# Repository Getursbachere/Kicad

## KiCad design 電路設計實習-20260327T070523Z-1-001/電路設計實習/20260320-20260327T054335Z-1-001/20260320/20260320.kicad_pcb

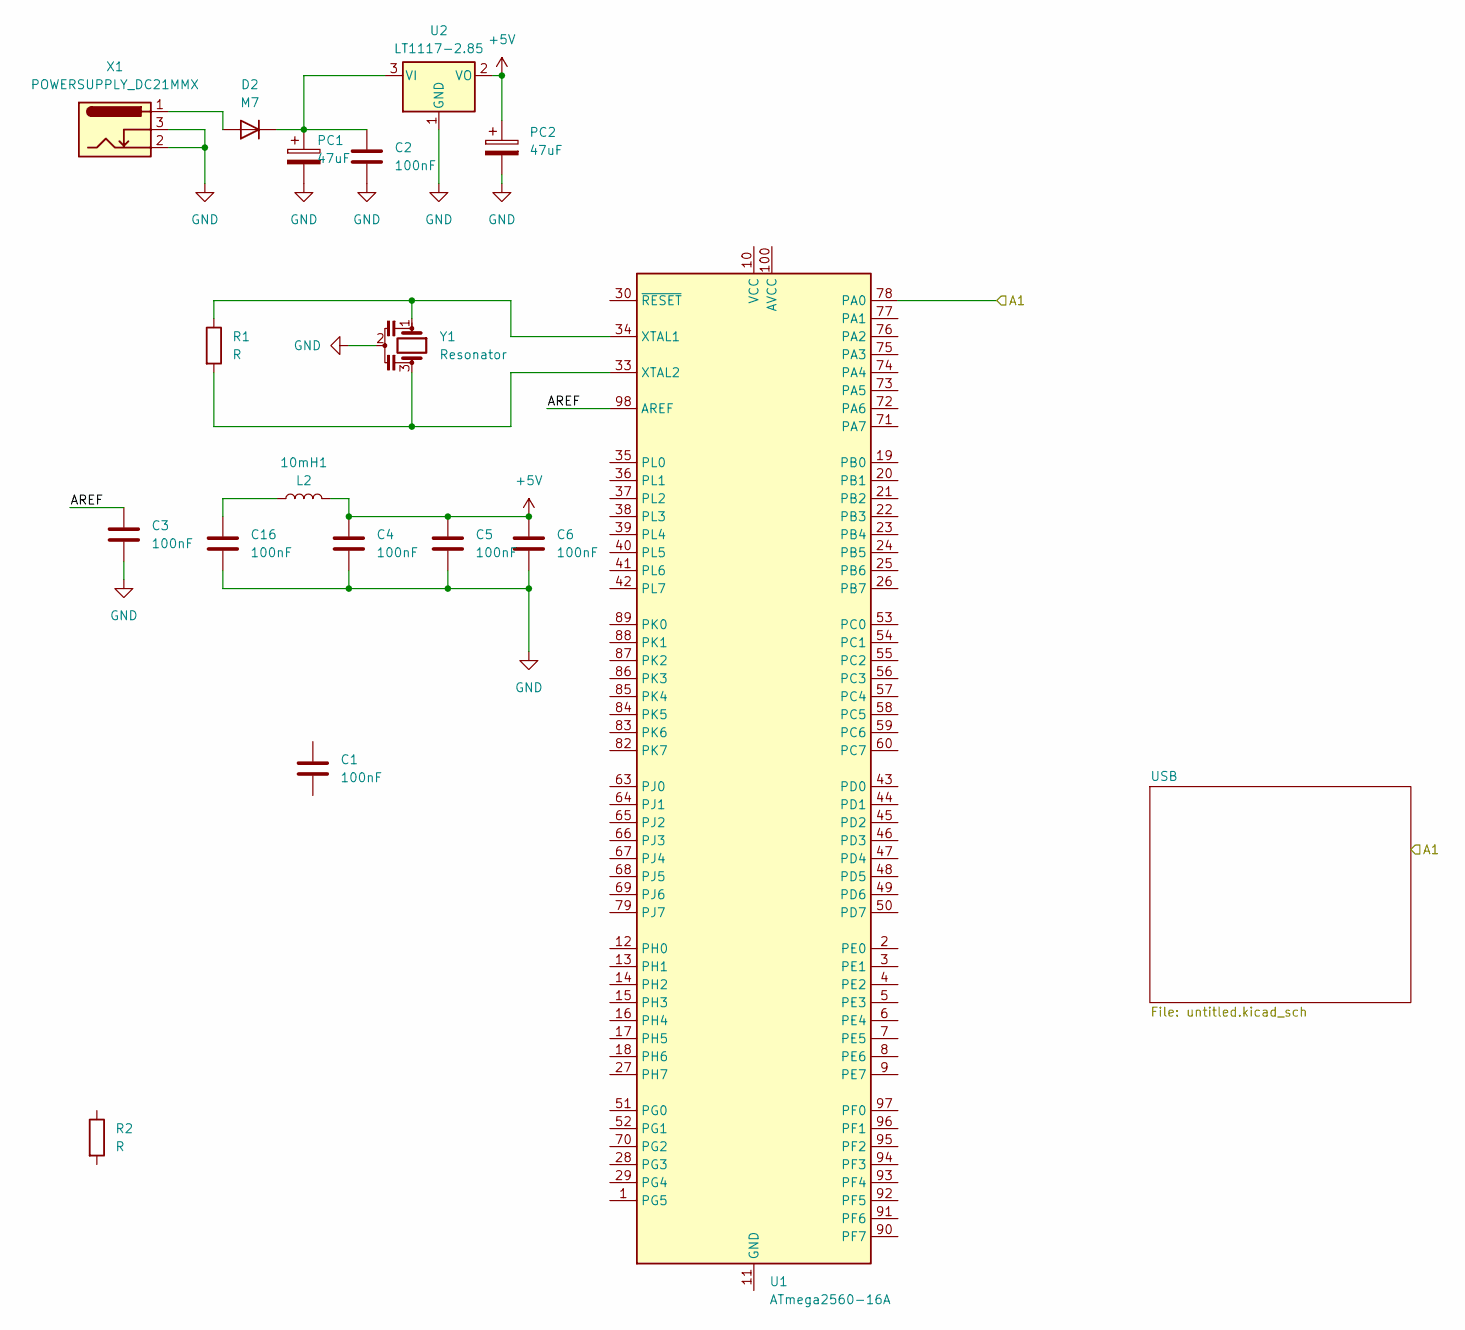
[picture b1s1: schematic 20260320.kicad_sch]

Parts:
10mH1: L2; L_0805_2012Metric
C1, C2, C3, C4, C5, C6, C16: 100nF; C_0603_1608Metric
D2: M7; D_SMB
PC1, PC2: 47uF; CP_Radial_D6.3mm_P2.50mm
R1, R2: R; R_0603_1608Metric
U1: ATmega2560-16A; TQFP-100_14x14mm_P0.5mm
U2: LT1117-2.85; SOT-223-3_TabPin2
X1: POWERSUPPLY_DC21MMX; BarrelJack_CUI_PJ-102AH_Horizontal
Y1: Resonator; Resonator_SMD_Murata_CSTxExxV-3Pin_3.0x1.1mm

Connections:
+5V: 10mH1.2, C4.1, C5.1, C6.1, PC2.1, U2.2 (VO); also elsewhere on the board
/A1: U1.78 (PA0)
/AREF: C3.1, U1.98 (AREF)
GND: C2.2, C3.2, C4.2, C5.2, C6.2, C16.2, PC1.2, PC2.2, U2.1 (GND), X1.2, X1.3, Y1.2; also elsewhere on the board
unnamed: 10mH1.1, C16.1
unnamed: D2.2 (A), X1.1
unnamed: C2.1, D2.1 (K), PC1.1, U2.3 (VI)
unnamed: U1.11 (GND), U1.32 (GND), U1.62 (GND), U1.81 (GND), U1.99 (GND)
unnamed: U1.10 (VCC), U1.31 (VCC), U1.61 (VCC), U1.80 (VCC)
unnamed: R1.1, U1.34 (XTAL1), Y1.1
unnamed: R1.2, U1.33 (XTAL2), Y1.3

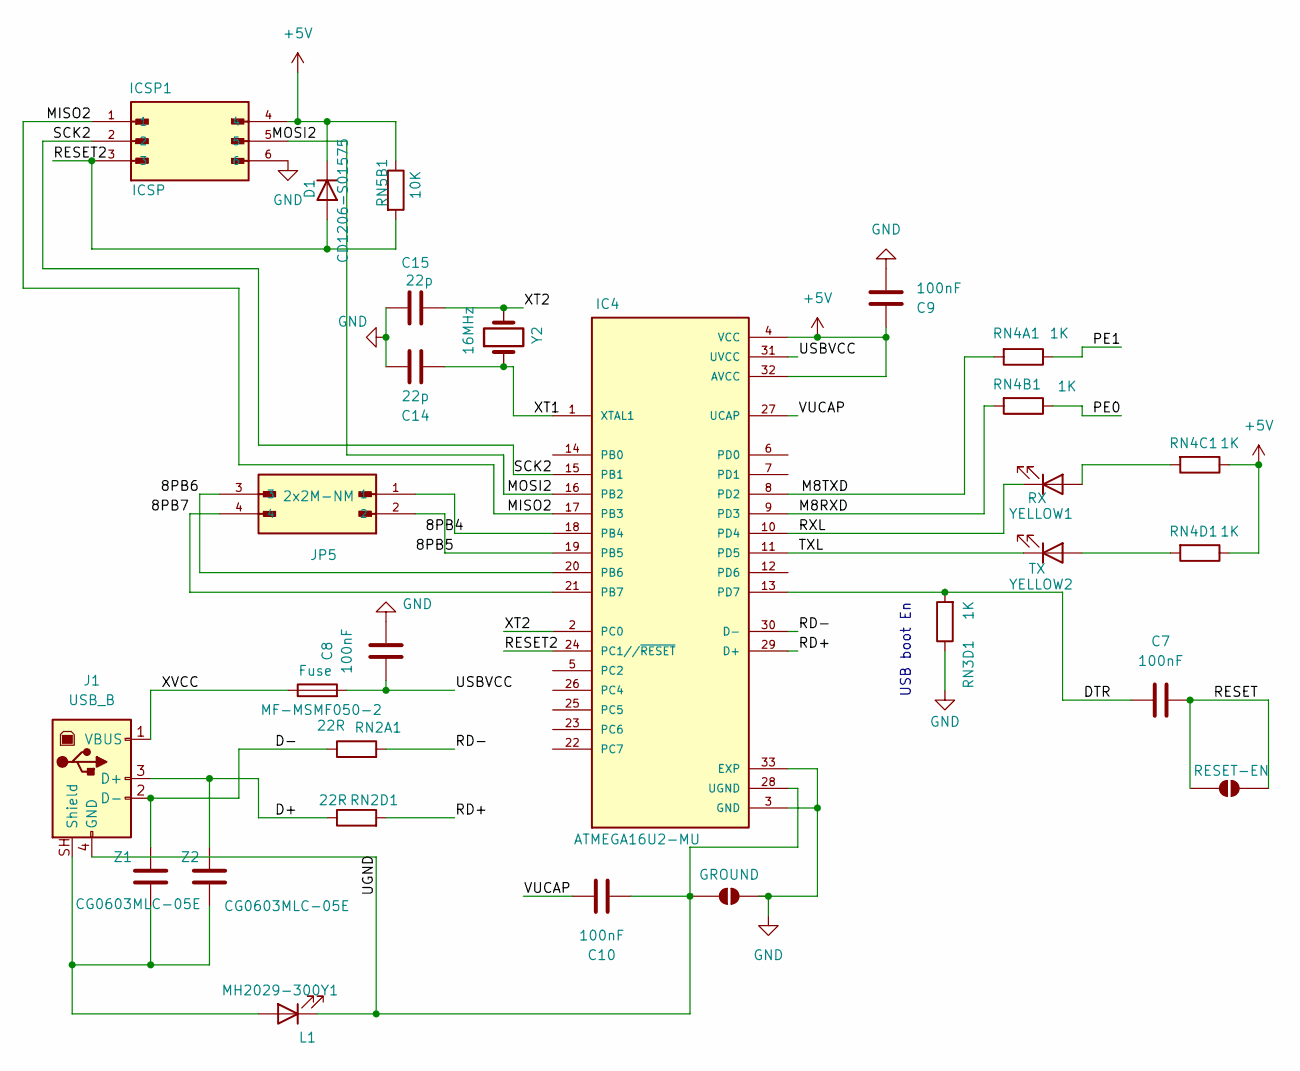
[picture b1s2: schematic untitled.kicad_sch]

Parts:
C7, C8, C9, C10: 100nF; C_0603_1608Metric
C14, C15: 22p; C_0603_1608Metric
D1: CD1206-S01575; D_MicroMELF
IC4: ATMEGA16U2-MU; QFN-32-1EP_5x5mm_P0.5mm_EP3.45x3.45mm
ICSP1: ICSP; MOLEX_2068320602; PARTREV A3
J1: USB_B; USB_B_Lumberg_2411_02_Horizontal
JP1: RESET-EN; SolderJumper-2_P1.3mm_Open_RoundedPad1.0x1.5mm
JP5: 2x2M-NM; PinHeader_2x02_P2.54mm_Vertical; PARTREV A3
MF-MSMF050-2: Fuse; Fuse_1812_4532Metric
MH2029-300Y1: L1; LED_0805_2012Metric
RN2A1, RN2D1: 22R; R_Array_SIP8
RN3D1, RN4A1, RN4B1, RN4C1, RN4D1: 1K; R_Array_SIP8
RN5B1: 10K; R_Array_SIP8
Y2: 16MHz; Crystal_SMD_0603-2Pin_6.0x3.5mm
YELLOW1: RX; LED_0805_2012Metric
YELLOW2: TX; LED_0805_2012Metric
Z1, Z2: CG0603MLC-05E; C_0603_1608Metric
a1: GROUND

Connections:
+5V: C9.1, D1.1 (K), IC4.4 (VCC), IC4.32 (AVCC), ICSP1.4, RN4C1.1, RN4D1.1, RN5B1.1; also elsewhere on the board
/USB/8PB4: IC4.18 (PB4), JP5.1
/USB/8PB5: IC4.19 (PB5), JP5.2
/USB/8PB6: IC4.20 (PB6), JP5.3
/USB/8PB7: IC4.21 (PB7), JP5.4
/USB/D+: J1.3 (D+), RN2D1.1, Z2.1
/USB/D-: J1.2 (D-), RN2A1.1, Z1.2
/USB/DTR: C7.1, IC4.13 (PD7), RN3D1.2
/USB/M8RXD: IC4.9 (PD3), RN4B1.2
/USB/M8TXD: IC4.8 (PD2), RN4A1.2
/USB/MISO2: IC4.17 (PB3), ICSP1.1
/USB/MOSI2: IC4.16 (PB2), ICSP1.5
/USB/PE0: RN4B1.1
/USB/PE1: RN4A1.1
/USB/RD+: IC4.29 (D+), RN2D1.2
/USB/RD-: IC4.30 (D-), RN2A1.2
/USB/RESET: C7.2, JP1.1 (A), JP1.2 (B)
/USB/RESET2: D1.2 (A), IC4.24 (PC1//~RESET), ICSP1.3, RN5B1.2
/USB/RXL: IC4.10 (PD4), YELLOW1.1 (K)
/USB/SCK2: IC4.15 (PB1), ICSP1.2
/USB/TXL: IC4.11 (PD5), YELLOW2.1 (K)
/USB/UGND: C10.1, IC4.28 (UGND), J1.4 (GND), MH2029-300Y1.1 (K), a1.2 (B)
/USB/USBVCC: C8.1, IC4.31 (UVCC), MF-MSMF050-2.2
/USB/VUCAP: C10.2, IC4.27 (UCAP)
/USB/XT1: C14.1, IC4.1 (XTAL1), Y2.1
/USB/XT2: C15.1, IC4.2 (PC0), Y2.2
/USB/XVCC: J1.1 (VBUS), MF-MSMF050-2.1
GND: C8.2, C9.2, C14.2, C15.2, IC4.3 (GND), IC4.33 (EXP), ICSP1.6, RN3D1.1, a1.1 (A); also elsewhere on the board
unnamed: J1.SH (Shield), MH2029-300Y1.2 (A), Z1.1, Z2.2
unnamed: RN4C1.2, YELLOW1.2 (A)
unnamed: RN4D1.2, YELLOW2.2 (A)

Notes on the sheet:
USB boot En

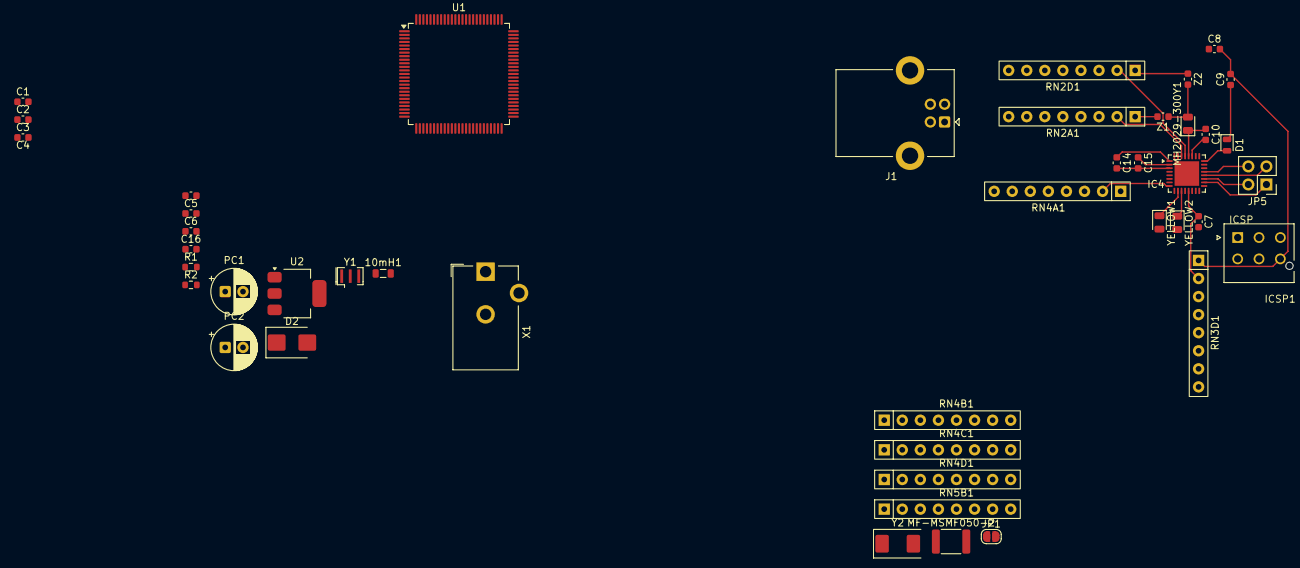
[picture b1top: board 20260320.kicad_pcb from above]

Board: 2 copper layers, 44 parts (0 on the bottom side), 37 nets.
